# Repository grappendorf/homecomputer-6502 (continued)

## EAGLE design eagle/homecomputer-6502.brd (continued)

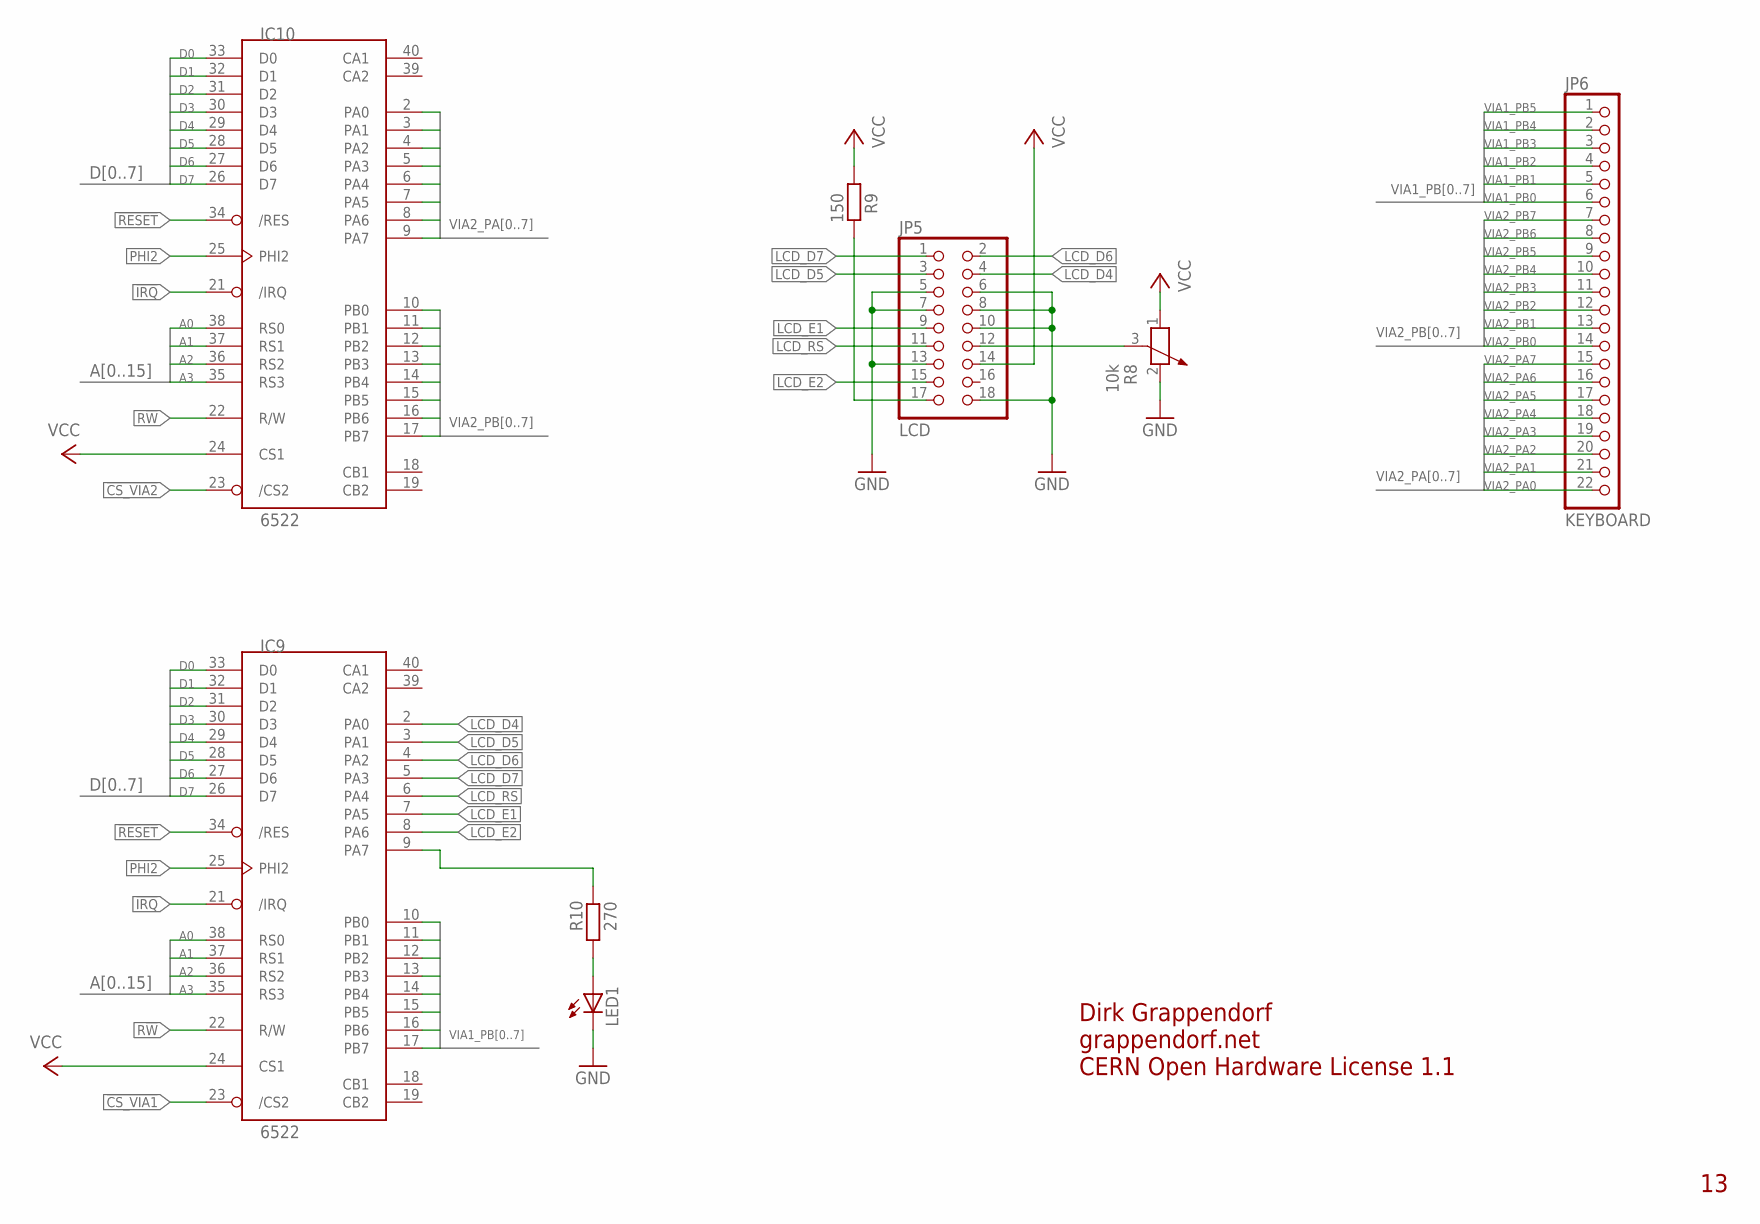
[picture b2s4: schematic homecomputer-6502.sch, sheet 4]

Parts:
IC9, IC10: 6522; DIP40
JP5: LCD; 2X09
JP6: KEYBOARD; 1X22
LED1: LED3MM
R8: 10k; PT-10
R9: 150; 0204/7
R10: 270; 0204/7

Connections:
!CS_VIA1: IC9.23 (/CS2); also elsewhere on the board
!CS_VIA2: IC10.23 (/CS2); also elsewhere on the board
!IRQ: IC9.21 (/IRQ), IC10.21 (/IRQ); also elsewhere on the board
!RESET: IC9.34 (/RES), IC10.34 (/RES); also elsewhere on the board
A0: IC9.38 (RS0), IC10.38 (RS0); also elsewhere on the board
A1: IC9.37 (RS1), IC10.37 (RS1); also elsewhere on the board
A2: IC9.36 (RS2), IC10.36 (RS2); also elsewhere on the board
A3: IC9.35 (RS3), IC10.35 (RS3); also elsewhere on the board
D0: IC9.33 (D0), IC10.33 (D0); also elsewhere on the board
D1: IC9.32 (D1), IC10.32 (D1); also elsewhere on the board
D2: IC9.31 (D2), IC10.31 (D2); also elsewhere on the board
D3: IC9.30 (D3), IC10.30 (D3); also elsewhere on the board
D4: IC9.29 (D4), IC10.29 (D4); also elsewhere on the board
D5: IC9.28 (D5), IC10.28 (D5); also elsewhere on the board
D6: IC9.27 (D6), IC10.27 (D6); also elsewhere on the board
D7: IC9.26 (D7), IC10.26 (D7); also elsewhere on the board
GND: JP5.5, JP5.6, JP5.7, JP5.8, JP5.10, JP5.13, JP5.18, LED1.K (C), R8.2; also elsewhere on the board
LCD_D4: IC9.2 (PA0), JP5.4
LCD_D5: IC9.3 (PA1), JP5.3
LCD_D6: IC9.4 (PA2), JP5.2
LCD_D7: IC9.5 (PA3), JP5.1
LCD_E1: IC9.7 (PA5), JP5.9
LCD_E2: IC9.8 (PA6), JP5.15
LCD_RS: IC9.6 (PA4), JP5.11
unnamed: IC9.9 (PA7), R10.2
unnamed: JP5.12, R8.3
unnamed: JP5.17, R9.2
unnamed: LED1.A, R10.1
PHI2: IC9.25 (PHI2), IC10.25 (PHI2); also elsewhere on the board
R!W: IC9.22 (R/W), IC10.22 (R/W); also elsewhere on the board
VCC: IC9.24 (CS1), IC10.24 (CS1), JP5.14, R8.1, R9.1; also elsewhere on the board
VIA1_PB0: IC9.10 (PB0), JP6.6
VIA1_PB1: IC9.11 (PB1), JP6.5
VIA1_PB2: IC9.12 (PB2), JP6.4
VIA1_PB3: IC9.13 (PB3), JP6.3
VIA1_PB4: IC9.14 (PB4), JP6.2
VIA1_PB5: IC9.15 (PB5), JP6.1
VIA1_PB6: IC9.16 (PB6)
VIA1_PB7: IC9.17 (PB7)
VIA2_PA0: IC10.2 (PA0), JP6.22
VIA2_PA1: IC10.3 (PA1), JP6.21
VIA2_PA2: IC10.4 (PA2), JP6.20
VIA2_PA3: IC10.5 (PA3), JP6.19
VIA2_PA4: IC10.6 (PA4), JP6.18
VIA2_PA5: IC10.7 (PA5), JP6.17
VIA2_PA6: IC10.8 (PA6), JP6.16
VIA2_PA7: IC10.9 (PA7), JP6.15
VIA2_PB0: IC10.10 (PB0), JP6.14
VIA2_PB1: IC10.11 (PB1), JP6.13
VIA2_PB2: IC10.12 (PB2), JP6.12
VIA2_PB3: IC10.13 (PB3), JP6.11
VIA2_PB4: IC10.14 (PB4), JP6.10
VIA2_PB5: IC10.15 (PB5), JP6.9
VIA2_PB6: IC10.16 (PB6), JP6.8
VIA2_PB7: IC10.17 (PB7), JP6.7

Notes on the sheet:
Dirk Grappendorf
grappendorf.net
CERN Open Hardware License 1.1

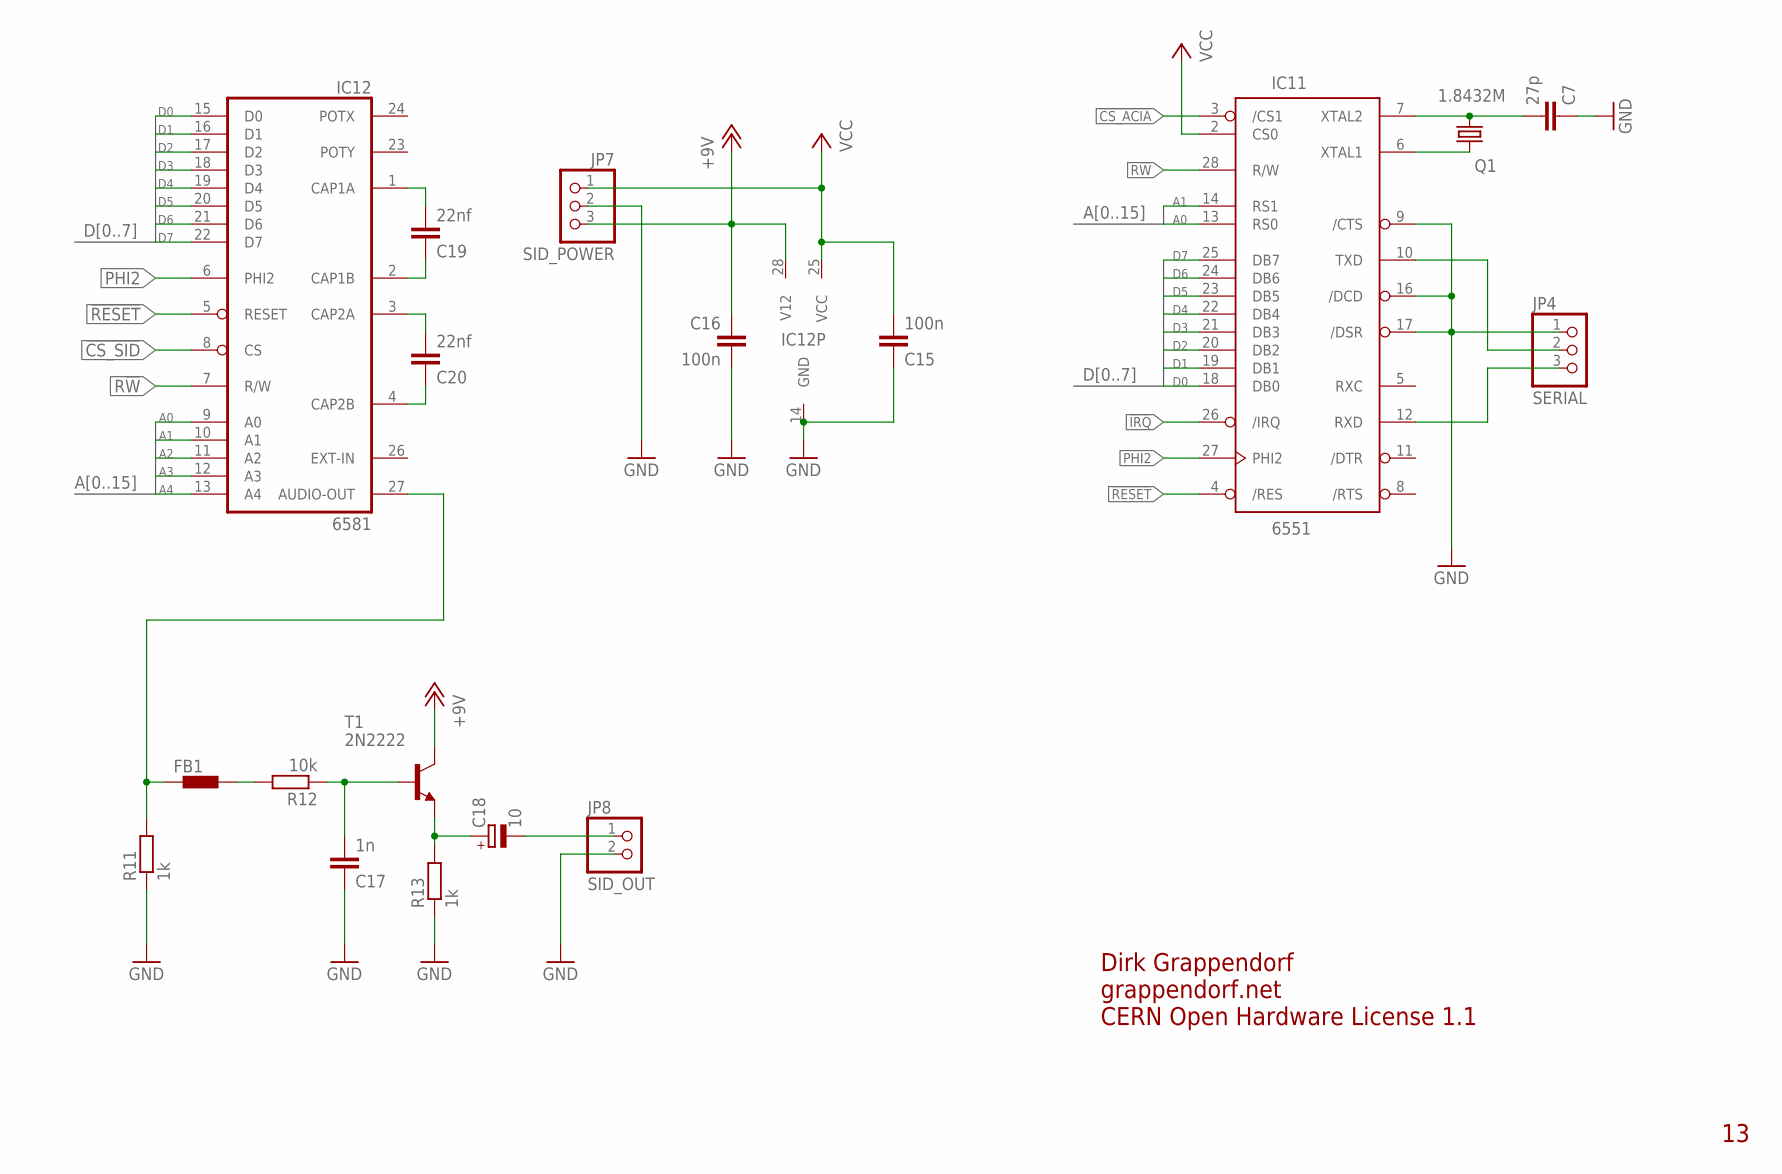
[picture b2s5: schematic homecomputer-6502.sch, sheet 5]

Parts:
C7: 27p; C025-024X044
C15, C16: 100n; C025-024X044
C17: 1n; C025-024X044
C18: 10; E2,5-5
C19, C20: 22nf; C025-024X044
FB1: BL01RN1A
IC11: 6551; DIP28
IC12: 6581; DIL28
JP4: SERIAL; 1X03
JP7: SID_POWER; 1X03
JP8: SID_OUT; 1X02
Q1: 1.8432M; HC49U-V
R11: 1k; 0204/7
R12: 10k; 0204/7
R13: 1k; 0204/5
T1: 2N2222; TO18

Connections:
!CS_ACIA: IC11.3 (/CS1); also elsewhere on the board
!CS_SID: IC12.8 (CS); also elsewhere on the board
!IRQ: IC11.26 (/IRQ); also elsewhere on the board
!RESET: IC11.4 (/RES), IC12.5 (RESET); also elsewhere on the board
+12V: C16.1, IC12.28 (V12), JP7.3, T1.3 (C)
A0: IC11.13 (RS0), IC12.9 (A0); also elsewhere on the board
A1: IC11.14 (RS1), IC12.10 (A1); also elsewhere on the board
A2: IC12.11 (A2); also elsewhere on the board
A3: IC12.12 (A3); also elsewhere on the board
A4: IC12.13 (A4); also elsewhere on the board
D0: IC11.18 (DB0), IC12.15 (D0); also elsewhere on the board
D1: IC11.19 (DB1), IC12.16 (D1); also elsewhere on the board
D2: IC11.20 (DB2), IC12.17 (D2); also elsewhere on the board
D3: IC11.21 (DB3), IC12.18 (D3); also elsewhere on the board
D4: IC11.22 (DB4), IC12.19 (D4); also elsewhere on the board
D5: IC11.23 (DB5), IC12.20 (D5); also elsewhere on the board
D6: IC11.24 (DB6), IC12.21 (D6); also elsewhere on the board
D7: IC11.25 (DB7), IC12.22 (D7); also elsewhere on the board
GND: C7.1, C15.1, C16.2, C17.1, IC11.9 (/CTS), IC11.16 (/DCD), IC11.17 (/DSR), IC12.14 (GND), JP4.1, JP7.2, JP8.2, R11.1, R13.1; also elsewhere on the board
unnamed: C7.2, IC11.7 (XTAL2), Q1.2
unnamed: IC11.6 (XTAL1), Q1.1
unnamed: IC11.10 (TXD), JP4.2
unnamed: IC11.12 (RXD), JP4.3
unnamed: FB1.1, IC12.27 (AUDIO-OUT), R11.2
unnamed: C19.2, IC12.1 (CAP1A)
unnamed: FB1.2, R12.2
unnamed: C17.2, R12.1, T1.2 (B)
unnamed: C18.+, R13.2, T1.1 (E)
unnamed: C18.-, JP8.1
unnamed: C19.1, IC12.2 (CAP1B)
unnamed: C20.2, IC12.3 (CAP2A)
unnamed: C20.1, IC12.4 (CAP2B)
PHI2: IC11.27 (PHI2), IC12.6 (PHI2); also elsewhere on the board
R!W: IC11.28 (R/W), IC12.7 (R/W); also elsewhere on the board
VCC: C15.2, IC11.2 (CS0), IC12.25 (VCC), JP7.1; also elsewhere on the board

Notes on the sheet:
Dirk Grappendorf
grappendorf.net
CERN Open Hardware License 1.1

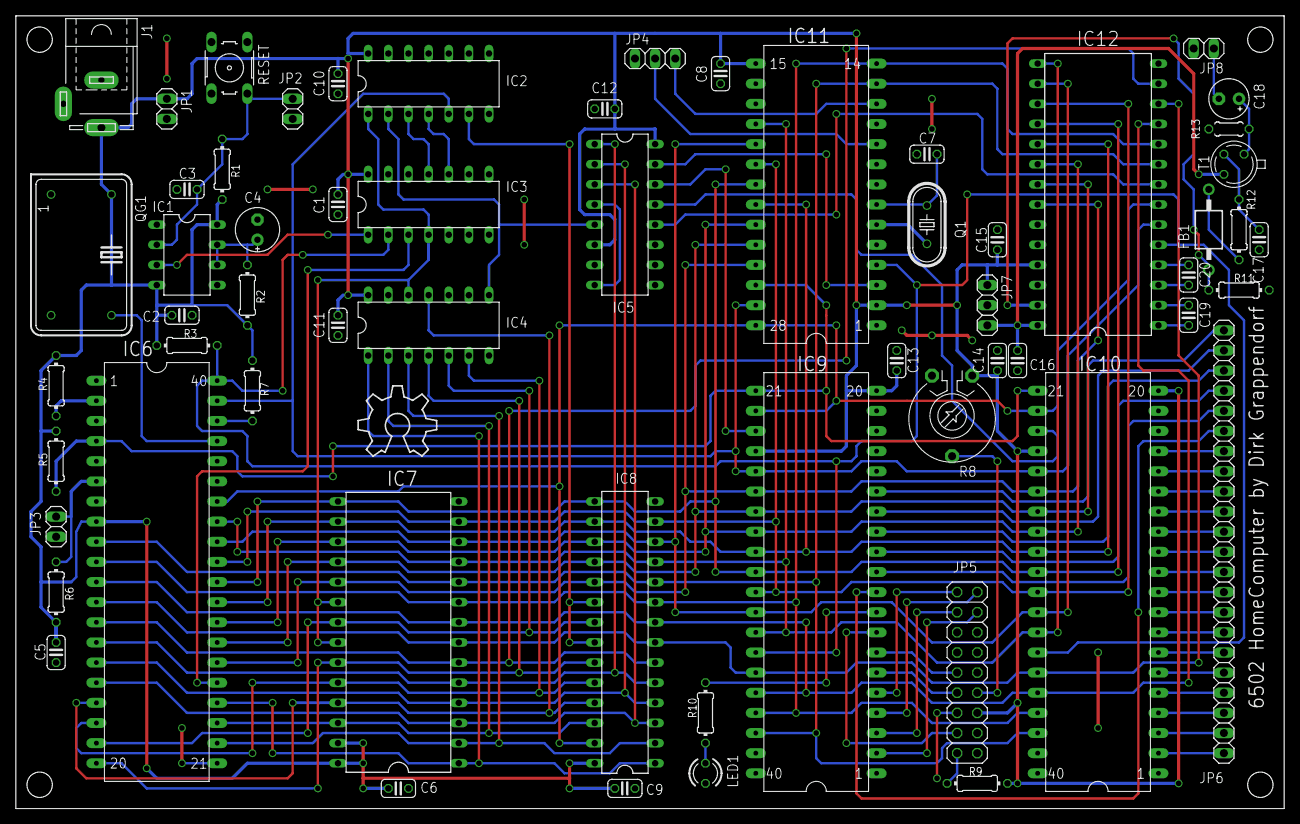
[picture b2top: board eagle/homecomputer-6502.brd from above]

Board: 2 copper layers, 160.0 x 100.0 mm, 61 parts (0 on the bottom side), 93 nets.

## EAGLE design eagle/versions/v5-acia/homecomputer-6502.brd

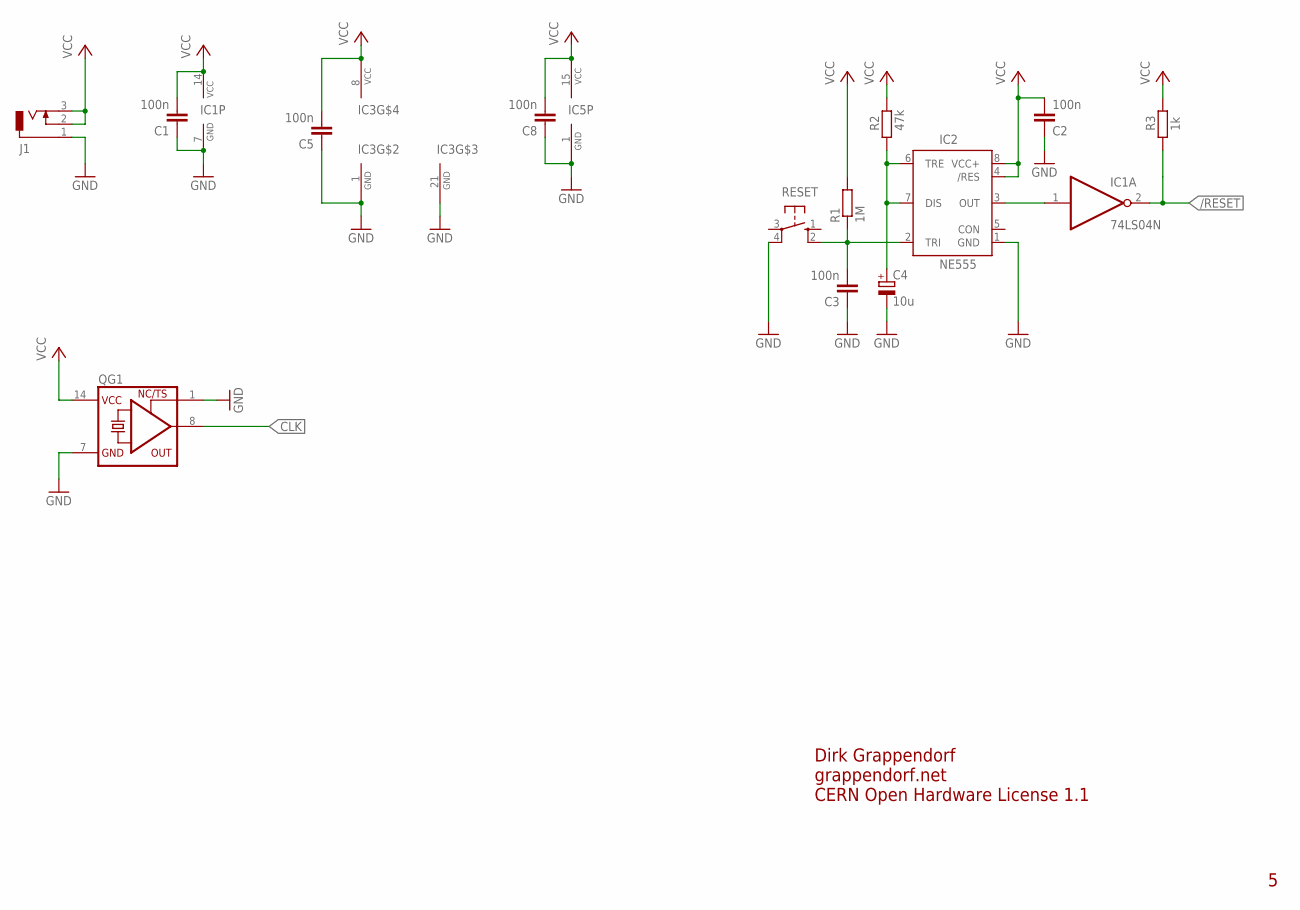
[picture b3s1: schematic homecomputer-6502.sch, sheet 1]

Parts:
C1, C2, C3, C5, C8: 100n; C025-024X044
C4: 10u; E2,5-6E
IC1: 74LS04N; DIL14
IC2: NE555; DIL-08
IC3: 6502; DIP40
IC5: 6551; DIP28
J1: DCJ0303
QG1: XO-14; DIL14S
R1: 1M; 0204/5
R2: 47k; 0204/5
R3: 1k; 0204/5
RESET: 10-XX; B3F-10XX

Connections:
/RESET: IC1.2 (O), R3.1; also elsewhere on the board
CLK: QG1.8 (OUT); also elsewhere on the board
GND: C1.1, C2.1, C3.1, C4.-, C5.1, C8.1, IC1.7 (GND), IC2.1 (GND), IC3.1 (GND), IC3.21 (GND), IC5.1 (GND), J1.1, QG1.1 (TS), QG1.7 (GND), RESET.4 (P1); also elsewhere on the board
unnamed: C4.+, IC2.6 (TRE), IC2.7 (DIS), R2.1
unnamed: IC1.1 (I), IC2.3 (OUT)
unnamed: C3.2, IC2.2 (TRI), R1.1, RESET.2 (S1)
VCC: C1.2, C2.2, C5.2, C8.2, IC1.14 (VCC), IC2.4 (/RES), IC2.8 (VCC+), IC3.8 (VCC), IC5.15 (VCC), J1.2, J1.3, QG1.14 (VCC), R1.2, R2.2, R3.2; also elsewhere on the board

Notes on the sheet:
Dirk Grappendorf
grappendorf.net
CERN Open Hardware License 1.1

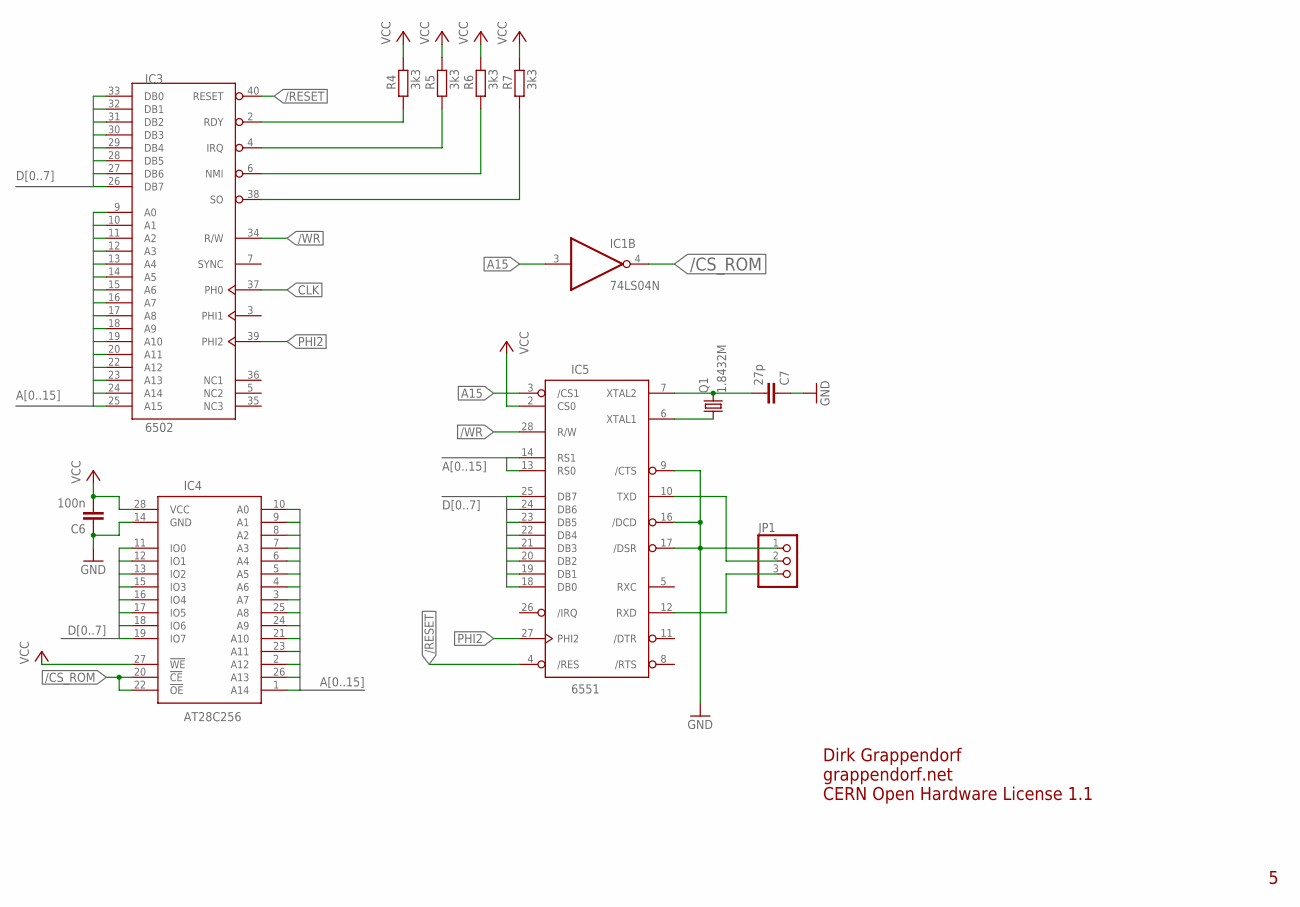
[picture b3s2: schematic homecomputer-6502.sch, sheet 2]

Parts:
C6: 100n; C025-024X044
C7: 27p; C025-024X044
IC1: 74LS04N; DIL14
IC3: 6502; DIP40
IC4: AT28C256; DIL28-6
IC5: 6551; DIP28
JP1: PINHD-1X3_2.54; 1X03
Q1: 1.8432M; HC49U-V
R4, R5, R6, R7: 3k3; 0204/5

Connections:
/CS_ROM: IC1.4 (O), IC4.20 (!CE), IC4.22 (!OE)
/RESET: IC3.40 (RESET), IC5.4 (/RES); also elsewhere on the board
/WR: IC3.34 (R/W), IC5.28 (R/W)
A0: IC3.9 (A0), IC4.10 (A0), IC5.13 (RS0)
A1: IC3.10 (A1), IC4.9 (A1), IC5.14 (RS1)
A2: IC3.11 (A2), IC4.8 (A2)
A3: IC3.12 (A3), IC4.7 (A3)
A4: IC3.13 (A4), IC4.6 (A4)
A5: IC3.14 (A5), IC4.5 (A5)
A6: IC3.15 (A6), IC4.4 (A6)
A7: IC3.16 (A7), IC4.3 (A7)
A8: IC3.17 (A8), IC4.25 (A8)
A9: IC3.18 (A9), IC4.24 (A9)
A10: IC3.19 (A10), IC4.21 (A10)
A11: IC3.20 (A11), IC4.23 (A11)
A12: IC3.22 (A12), IC4.2 (A12)
A13: IC3.23 (A13), IC4.26 (A13)
A14: IC3.24 (A14), IC4.1 (A14)
A15: IC1.3 (I), IC3.25 (A15), IC5.3 (/CS1)
CLK: IC3.37 (PH0); also elsewhere on the board
D0: IC3.33 (DB0), IC4.11 (IO0), IC5.18 (DB0)
D1: IC3.32 (DB1), IC4.12 (IO1), IC5.19 (DB1)
D2: IC3.31 (DB2), IC4.13 (IO2), IC5.20 (DB2)
D3: IC3.30 (DB3), IC4.15 (IO3), IC5.21 (DB3)
D4: IC3.29 (DB4), IC4.16 (IO4), IC5.22 (DB4)
D5: IC3.28 (DB5), IC4.17 (IO5), IC5.23 (DB5)
D6: IC3.27 (DB6), IC4.18 (IO6), IC5.24 (DB6)
D7: IC3.26 (DB7), IC4.19 (IO7), IC5.25 (DB7)
GND: C6.1, C7.1, IC4.14 (GND), IC5.9 (/CTS), IC5.16 (/DCD), IC5.17 (/DSR), JP1.1; also elsewhere on the board
unnamed: C7.2, IC5.7 (XTAL2), Q1.2
unnamed: IC5.6 (XTAL1), Q1.1
unnamed: IC3.2 (RDY), R4.1
unnamed: IC5.10 (TXD), JP1.2
unnamed: IC3.4 (IRQ), R5.1
unnamed: IC3.6 (NMI), R6.1
unnamed: IC3.38 (SO), R7.1
unnamed: IC5.12 (RXD), JP1.3
PHI2: IC3.39 (PHI2), IC5.27 (PHI2)
VCC: C6.2, IC4.27 (!WE), IC4.28 (VCC), IC5.2 (CS0), R4.2, R5.2, R6.2, R7.2; also elsewhere on the board

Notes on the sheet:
Dirk Grappendorf
grappendorf.net
CERN Open Hardware License 1.1

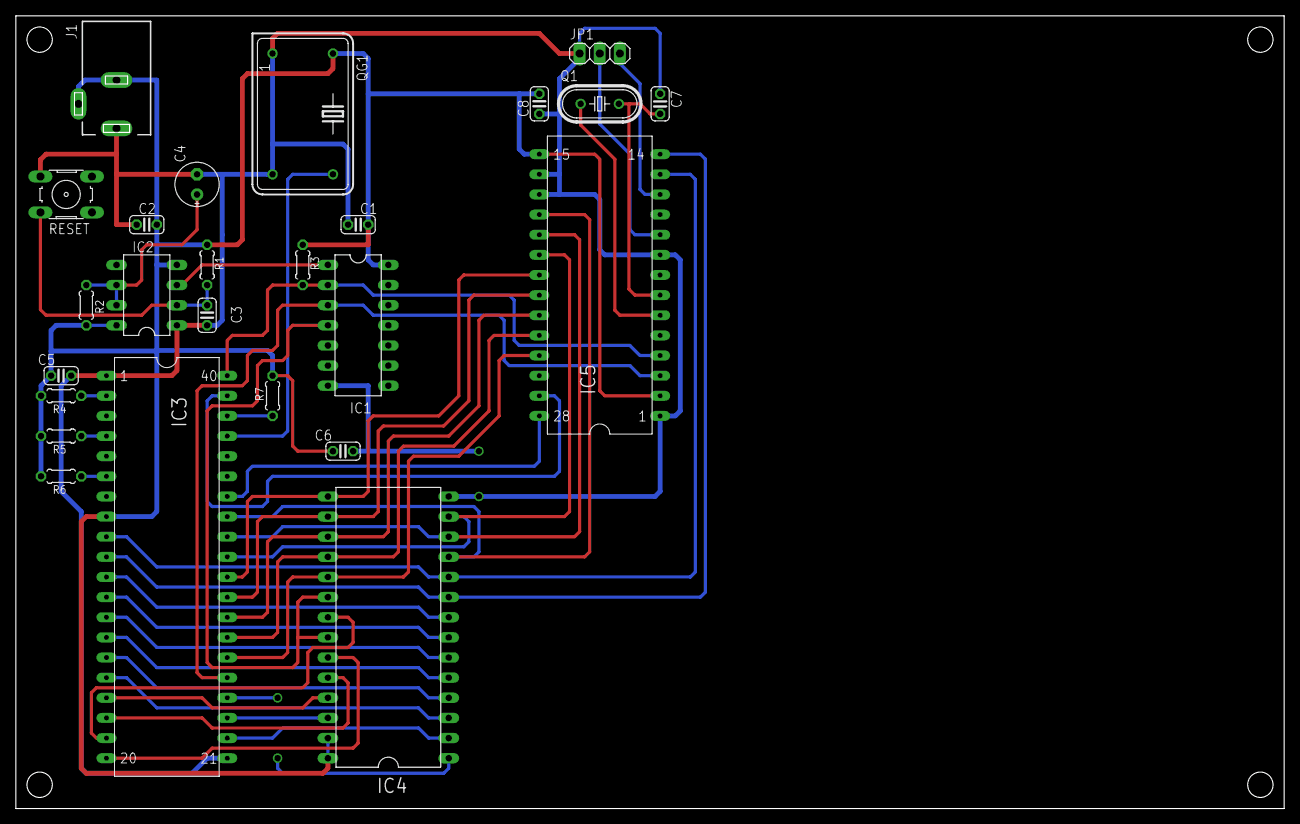
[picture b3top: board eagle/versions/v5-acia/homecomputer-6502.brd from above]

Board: 3 copper layers, 160.0 x 100.0 mm, 25 parts (0 on the bottom side), 42 nets.

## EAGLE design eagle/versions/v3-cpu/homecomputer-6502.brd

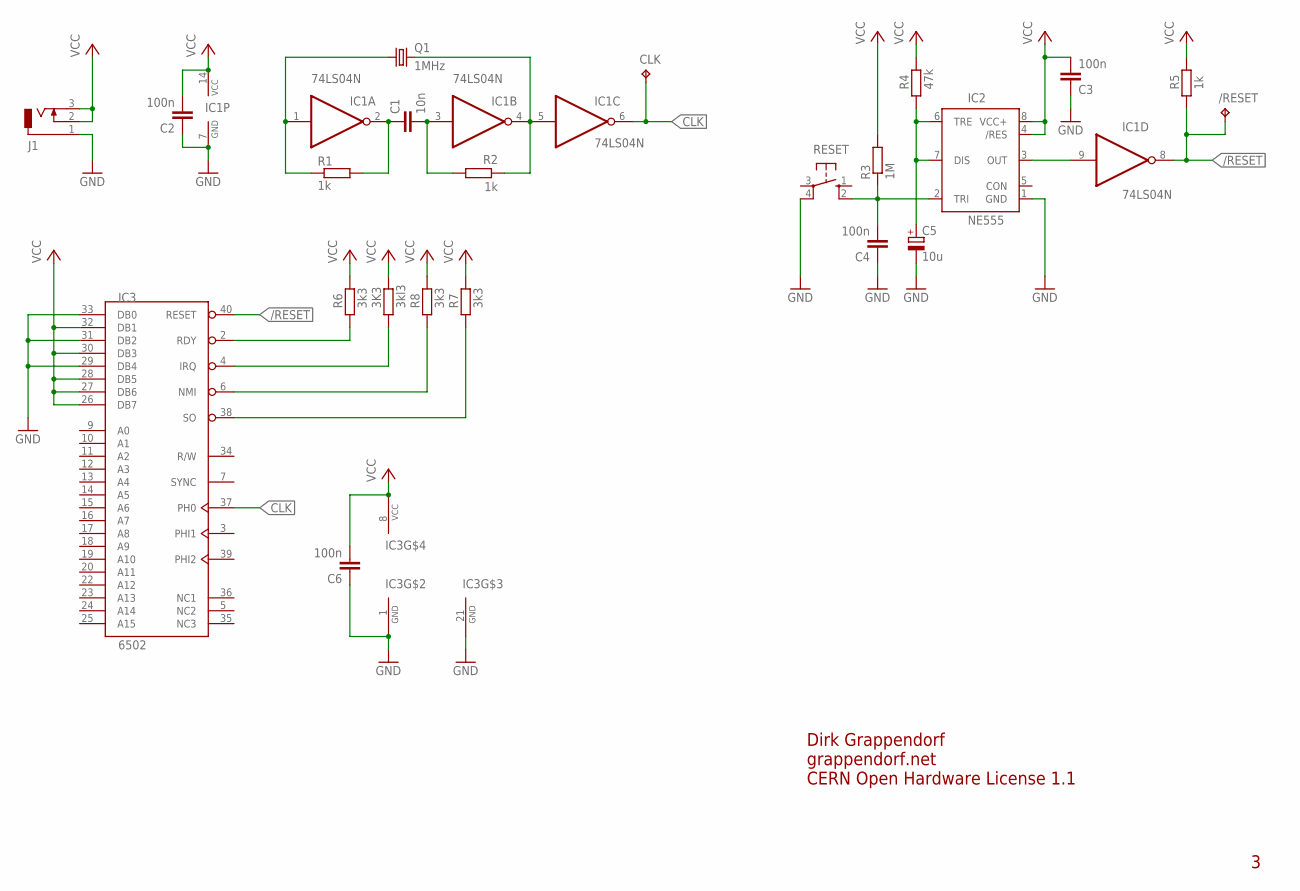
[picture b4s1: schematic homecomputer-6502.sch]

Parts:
3K3: 3kl3; 0204/5
/RESET: TPPAD1-13; P1-13
C1: 10n; C025-024X044
C2, C3, C4, C6: 100n; C025-024X044
C5: 10u; E2,5-6E
CLK: TPPAD1-13; P1-13
IC1: 74LS04N; DIL14
IC2: NE555; DIL-08
IC3: 6502; DIP40
J1: DCJ0303
Q1: 1MHz; HC49U-V
R1, R2, R5: 1k; 0204/5
R3: 1M; 0204/5
R4: 47k; 0204/5
R6, R7, R8: 3k3; 0204/5
RESET: 10-XX; B3F-10XX

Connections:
/RESET: /RESET.TP, IC1.8 (O), IC3.40 (RESET), R5.1
CLK: CLK.TP, IC1.6 (O), IC3.37 (PH0)
GND: C2.1, C3.1, C4.1, C5.-, C6.1, IC1.7 (GND), IC2.1 (GND), IC3.1 (GND), IC3.21 (GND), IC3.29 (DB4), IC3.31 (DB2), IC3.33 (DB0), J1.1, RESET.4 (P1)
unnamed: IC1.1 (I), Q1.1, R1.1
unnamed: C1.1, IC1.2 (O), R1.2
unnamed: IC3.2 (RDY), R6.1
unnamed: C5.+, IC2.6 (TRE), IC2.7 (DIS), R4.1
unnamed: IC1.9 (I), IC2.3 (OUT)
unnamed: C4.2, IC2.2 (TRI), R3.1, RESET.2 (S1)
unnamed: C1.2, IC1.3 (I), R2.2
unnamed: IC1.4 (O), IC1.5 (I), Q1.2, R2.1
unnamed: 3K3.1, IC3.4 (IRQ)
unnamed: IC3.6 (NMI), R8.1
unnamed: IC3.38 (SO), R7.1
VCC: 3K3.2, C2.2, C3.2, C6.2, IC1.14 (VCC), IC2.4 (/RES), IC2.8 (VCC+), IC3.8 (VCC), IC3.26 (DB7), IC3.27 (DB6), IC3.28 (DB5), IC3.30 (DB3), IC3.32 (DB1), J1.2, J1.3, R3.2, R4.2, R5.2, R6.2, R7.2, R8.2

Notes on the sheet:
Dirk Grappendorf
grappendorf.net
CERN Open Hardware License 1.1

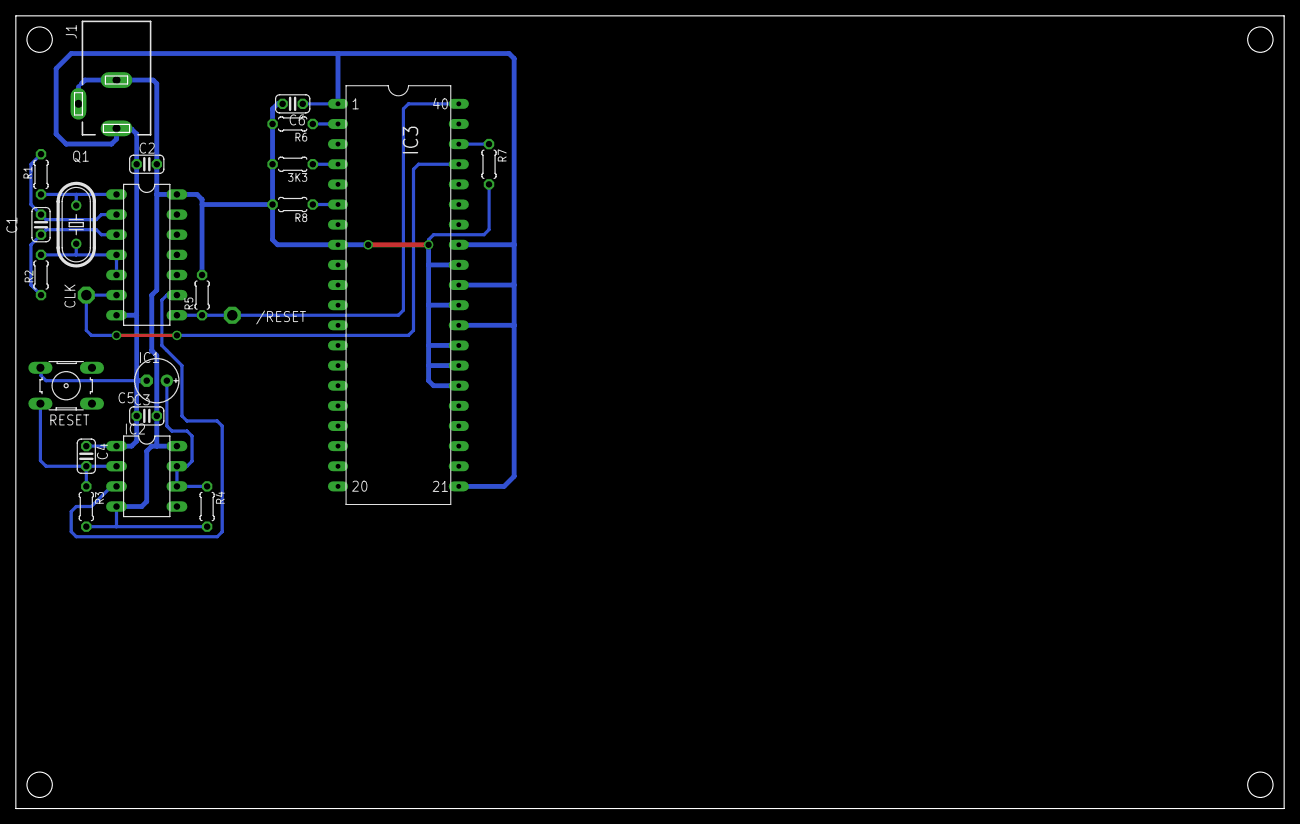
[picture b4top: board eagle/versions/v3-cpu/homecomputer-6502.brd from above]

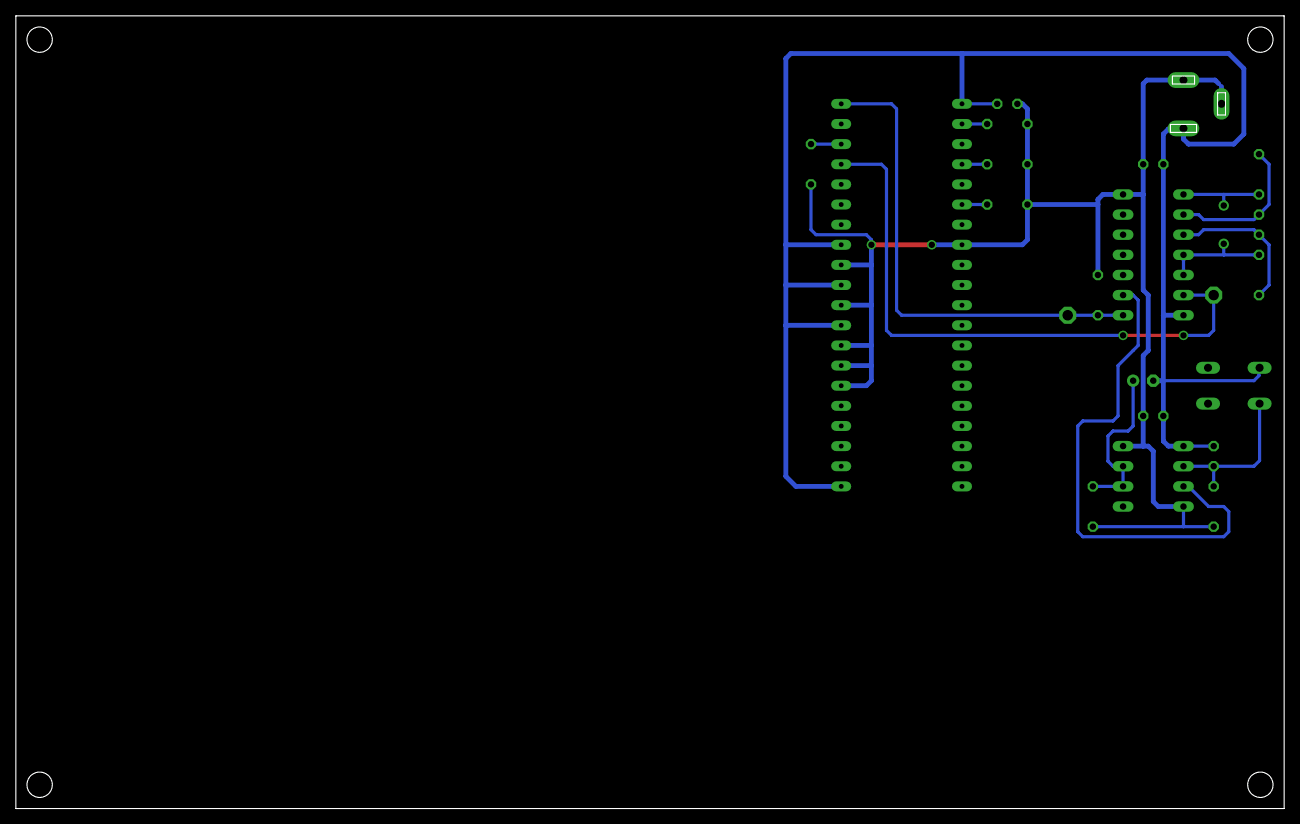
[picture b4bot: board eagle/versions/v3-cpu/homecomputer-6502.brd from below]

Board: 2 copper layers, 160.0 x 100.0 mm, 23 parts (2 on the bottom side), 15 nets.

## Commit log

2015-01-04 Rename BASIC interpreter main function to interpret()
2015-01-04 Add a function that parses string arguments
2015-01-04 Skip whitespace between line number and command and between the command and its arguments.
2015-01-04 Fix: Wrong char for SHIFT+0 (should be '=' instead of '0')
2015-01-04 Add variables: LET sets a variable, VARS lists all variables, CLEAR clears all variables and PRINT can print a variable.
2015-01-04 Add command PRINTLN which prints with newline. Now PRINT prints without newline.
2015-01-04 Fix: Wrong char for SHIFT+I (should be 'I' instead of 'i')
2015-01-04 Fix: Wrong char for SHIFT+ß (should be '?' instead of 'ß')
2015-01-04 Add new command INPUT which reads keyboard input into a variable. More verbose print for the SAVE command.
2015-01-06 Extract keyboard line reading into seperate module, cleanup main() and cmd_input()
2015-01-06 Rename command PRINTLN to PRINT and PRINT to PUT
2015-01-06 Show a "File not found!" error when a file to load wasn't found LOAD and SAVE now expect a string argument ("...") Allow file extensions for LOAD and SAVE
2015-01-06 Add command DIR which lists all program files on the terminal host
2015-01-06 Optimization: parse_string() sets the terminating '"' character to '\0' and only returns a pointer to the parsed string, and a pointer behind the string argument Needed to change all const char * arg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
2015-01-06 Filter invalid UTF-8 chars that can accidentially arrive on the serial interface
2015-01-06 Optimize LCD performance (removed unneccessary delay loops)
2015-01-06 Fix: Running programs destroys string arguments After parse_string() the replaced '"' character must be restored
2015-01-07 The RUN command can now be interrupted (NMI) The LIST command can now be interrupted (NMI) and waits for a key press after each line The DIR command can now be interrupted (NMI) and waits for a key p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
2015-01-07 Cleanup DIR output and display program file size
2015-01-07 The SLEEP command can now be interrupted (NMI)
2015-01-07 Remove test.bas
2015-01-08 Add builtin variables Add builtin variable ti$ that returns the current time ("hh:mm:ss") Add builtin variable ti that returns the current time in milliseconds Remove commands TIME and UPTIME The VAR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
2015-01-08 Extract variable management code into separate module
2015-01-08 Add new command AT <x>,<y> for positioning the cursor
2015-01-08 Add new command CURSOR on|off to enable/disable the cursor
2015-01-08 Enable the cursor when a program was interrupted
2015-01-08 Refactor: Add function prototypes, reorder, add commentation
2015-01-08 Allow assignment of integer constants and integer variables to an integer variable Allow assignment of string constants and string variables to a string variable Refactor number/string expression par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
2015-01-08 Allow +-*/ in number expressions (currently without precendence)
2015-01-08 Revert messed up constant names
2015-01-08 Add random number variable rn Add random number generator SEED command
2015-01-08 Add modulo operator %
2015-01-08 Allow number expressions in the AT command
2015-01-08 Allow string expressions in LOAD and SAVE command
2015-01-08 Allow a comma separated list of arguments in the PRINT/PUT command
2015-01-08 Fix: Cannot press enter at the end of the readline buffer
2015-01-08 Add number comparison operator == Fix: Terminate PRINT/PUT command when an error occourred
2015-01-08 Add command IF (conditional command execution) Add command END (terminate program)
2015-01-09 In commands LET/LIST/DIR: don't need to press any key after the last line
2015-01-09 INPUT now accepts integer varibles and reads integer numbers
2015-01-09 Add number expression operators <,<=,>,>= Add a number guess BASIC program
2015-01-09 Readline input can now be entered on 2 display lines (79 characters)
2015-01-09 Clear the input buffer with Ctrl-U
2015-01-09 Add command EDIT that lets you edit a program line
2015-01-09 Improve readline navigation: Cursor left/right, Home/Ctrl-A, End/Ctrl-E Insert, Delete, Backspace at any point
2015-01-10 Add ONERROR <command> option the INPUT command INPUT repeats if an invalid number was entered for an integer variable, or executes the command if an ONERROR command was specified
2015-01-10 You can now use string comparisons in a number expression Improve reporting of invalid token syntax errors Add a string comparison BASIC program example
2015-01-10 Add command REM (line comment)
2015-01-10 Add new command WRITE that writes a character to the screen but does not move the cursor Use random function from the CC65 standard library Only print "Ready." messages when not running a program
2015-01-10 AT command can now read a character from the screen (AT x,y,var$) Add game of life BASIC program (currently not working because we don't have arrays)
2015-01-10 Add license files
2015-01-12 Update documentation
2015-01-13 docs: Add image to readme
2015-01-14 docs: Add program documentation
2015-01-19 docs: Add code documentation
2015-01-26 Add final schematics
2015-01-26 fix: Broken linkt to homepage
